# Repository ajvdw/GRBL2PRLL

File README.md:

# Eagle 8.1 Files for GRBL interface to a Chinese TB6520 4 axis driver

Schematics
Board 

Gerber-files

Not tested yet

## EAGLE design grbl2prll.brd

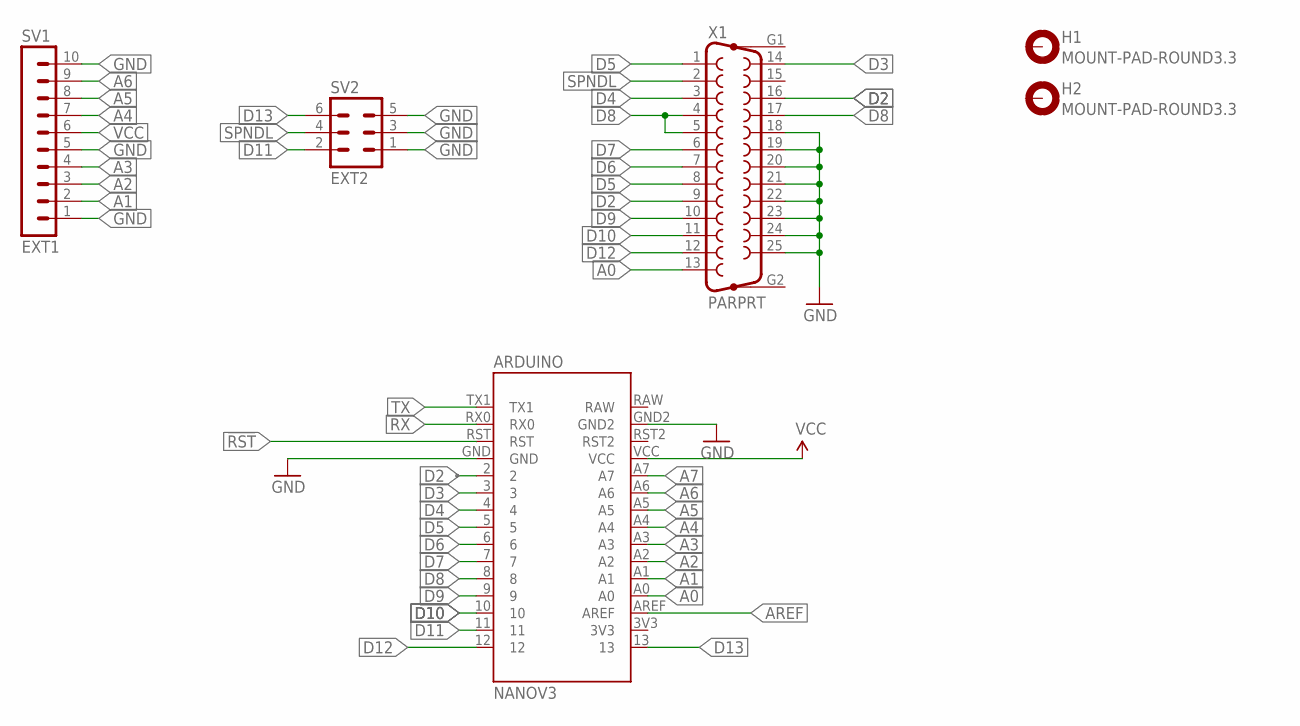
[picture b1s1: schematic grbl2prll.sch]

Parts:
ARDUINO: NANOV3
H1, H2: MOUNT-PAD-ROUND3.3; 3,3-PAD
SV1: EXT1; MA10-1
SV2: EXT2; MA03-2
X1: PARPRT; F25HP

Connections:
!RST: ARDUINO.RST
A0: ARDUINO.A0, X1.13
A1: ARDUINO.A1, SV1.2
A2: ARDUINO.A2, SV1.3
A3: ARDUINO.A3, SV1.4
A4: ARDUINO.A4, SV1.7
A5: ARDUINO.A5, SV1.8
A6: ARDUINO.A6, SV1.9
A7: ARDUINO.A7
AREF: ARDUINO.AREF
D2: ARDUINO.2, X1.9, X1.16
D3: ARDUINO.3, X1.14
D4: ARDUINO.4, X1.3
D5: ARDUINO.5, X1.1, X1.8
D6: ARDUINO.6, X1.7
D7: ARDUINO.7, X1.6
D8: ARDUINO.8, X1.4, X1.5, X1.17
D9: ARDUINO.9, X1.10
D10: ARDUINO.10, X1.11
D11: ARDUINO.11, SV2.2
D12: ARDUINO.12, X1.12
D13: ARDUINO.13, SV2.6
GND: ARDUINO.GND, ARDUINO.GND2, SV1.1, SV1.5, SV1.10, SV2.1, SV2.3, SV2.5, X1.18, X1.19, X1.20, X1.21, X1.22, X1.23, X1.24, X1.25
RX: ARDUINO.RX0
SPNDL: SV2.4, X1.2
TX: ARDUINO.TX1
VCC: ARDUINO.VCC, SV1.6

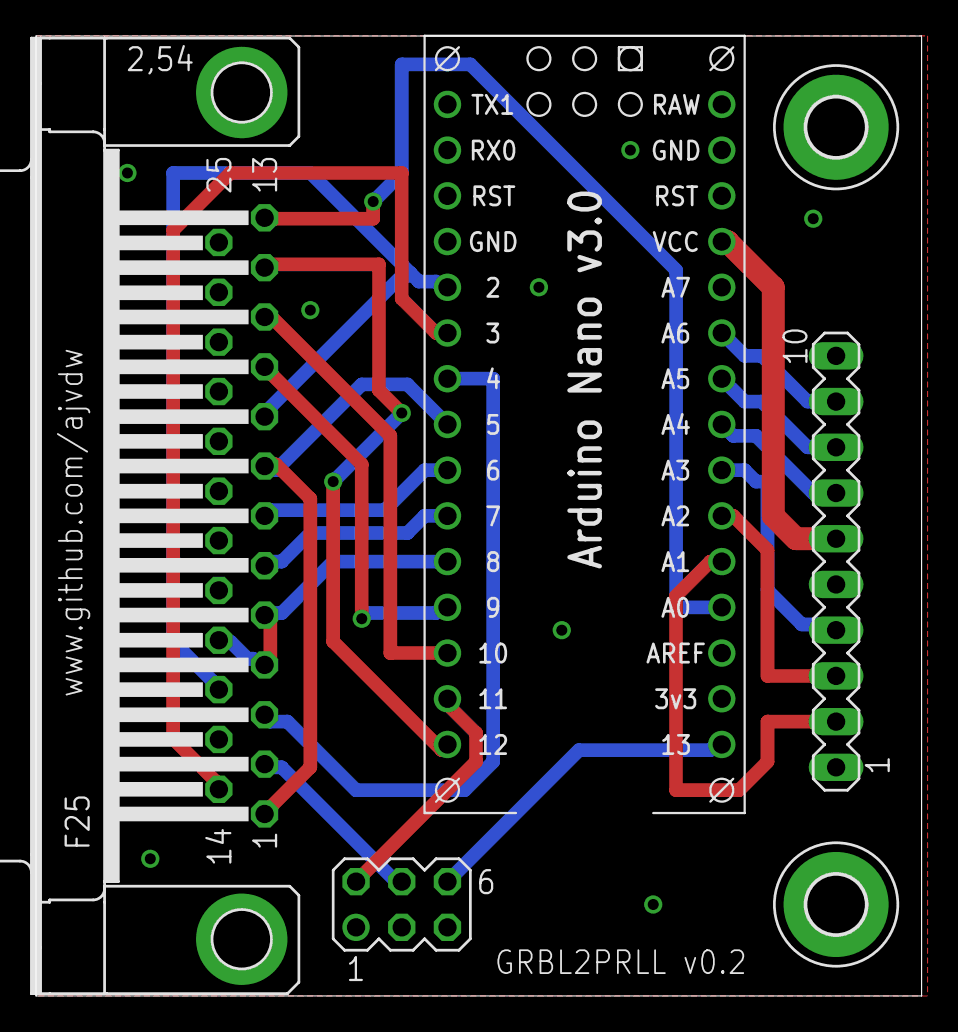
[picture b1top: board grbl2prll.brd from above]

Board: 2 copper layers, 49.2 x 53.3 mm, 6 parts (0 on the bottom side), 22 nets.

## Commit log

2017-03-19 Added read.me
2017-03-19 Minor changes in read.me
